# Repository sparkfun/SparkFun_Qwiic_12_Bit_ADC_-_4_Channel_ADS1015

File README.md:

SparkFun Qwiic ADC
========================================

[*SparkFun Qwiic 12 Bit ADC - 4 Channel ADS1015 (Sen-15334)*](https://www.sparkfun.com/products/15334)

Qwiic breakout board for the ADS1015 4-channel 12-bit ADC from TI.

A lot of the time you just need to add more analog inputs to solve a problem. It happens. The SparkFun Qwiic 12 Bit ADC can provide four channels of I2C controlled ADC input to your Qwiic enabled project. These channels can be used as single-ended inputs, or in pairs for differential inputs. What makes this even more powerful is that it has a programmable gain amplifier that lets you "zoom in" on a very small change in analog voltage (but will still effect your input range and resolution). Utilizing our handy Qwiic system, no soldering is required to connect it to the rest of your system. However, we still have broken out 0.1"-spaced pins in case you prefer to use a breadboard.

The ADS1015 uses its own internal voltage reference for measurements, but a ground and 3.3V reference are also available on the pin outs for users. This ADC board includes screw pin terminals on the four channels of input, allowing for solderless connection to voltage sources in your setup. It also has an address jumper that lets you choose one of four unique addresses (0x48, 0x49, 0x4A, 0x4B). With this, you can connect up to four of these on the same I2C bus and have sixteen channels of ADC. The maximum resolution of the converter is 12-bits in differential mode and 11-bits for single-ended inputs. Step sizes range from 125μV per count to 3mV per count depending on the full-scale range (FSR) setting.

We have included an onboard 10K trimpot connected to channel A3. This is handy for initial setup testing and can be used as a simple variable input to your project. But don't worry, we added an isolation jumper so you can use channel A3 however you'd like.

Repository Contents
-------------------

* **/Hardware** - Eagle design files (.brd, .sch)
* **/Production** - Production panel files (.brd)

Documentation
--------------
* **[Arduino Library for the ADS1015](https://github.com/sparkfun/SparkFun_ADS1015_Arduino_Library)** - Arduino library for the ADS1015.
* **[Hookup Guide](https://learn.sparkfun.com/tutorials/qwiic-12-bit-adc)** - Basic hookup guide for the SparkFun Qwiic 12 Bit ADC - 4 Channel ADS1015. Includes hardware overview, software installation instructions and overviews of each example in the arduino library.

License Information
-------------------

This product is _**open source**_! 

Please review the LICENSE.md file for license information. 

If you have any questions or concerns on licensing, please visit the [SparkFun Forum](https://forum.sparkfun.com/index.php) and post a topic. For more general questions related to our qwiic system, please visit this section of the forum: [SparkFun Forums: QWIIC SYSTEMS](https://forum.sparkfun.com/viewforum.php?f=105)

Distributed as-is; no warranty is given.

- Your friends at SparkFun.

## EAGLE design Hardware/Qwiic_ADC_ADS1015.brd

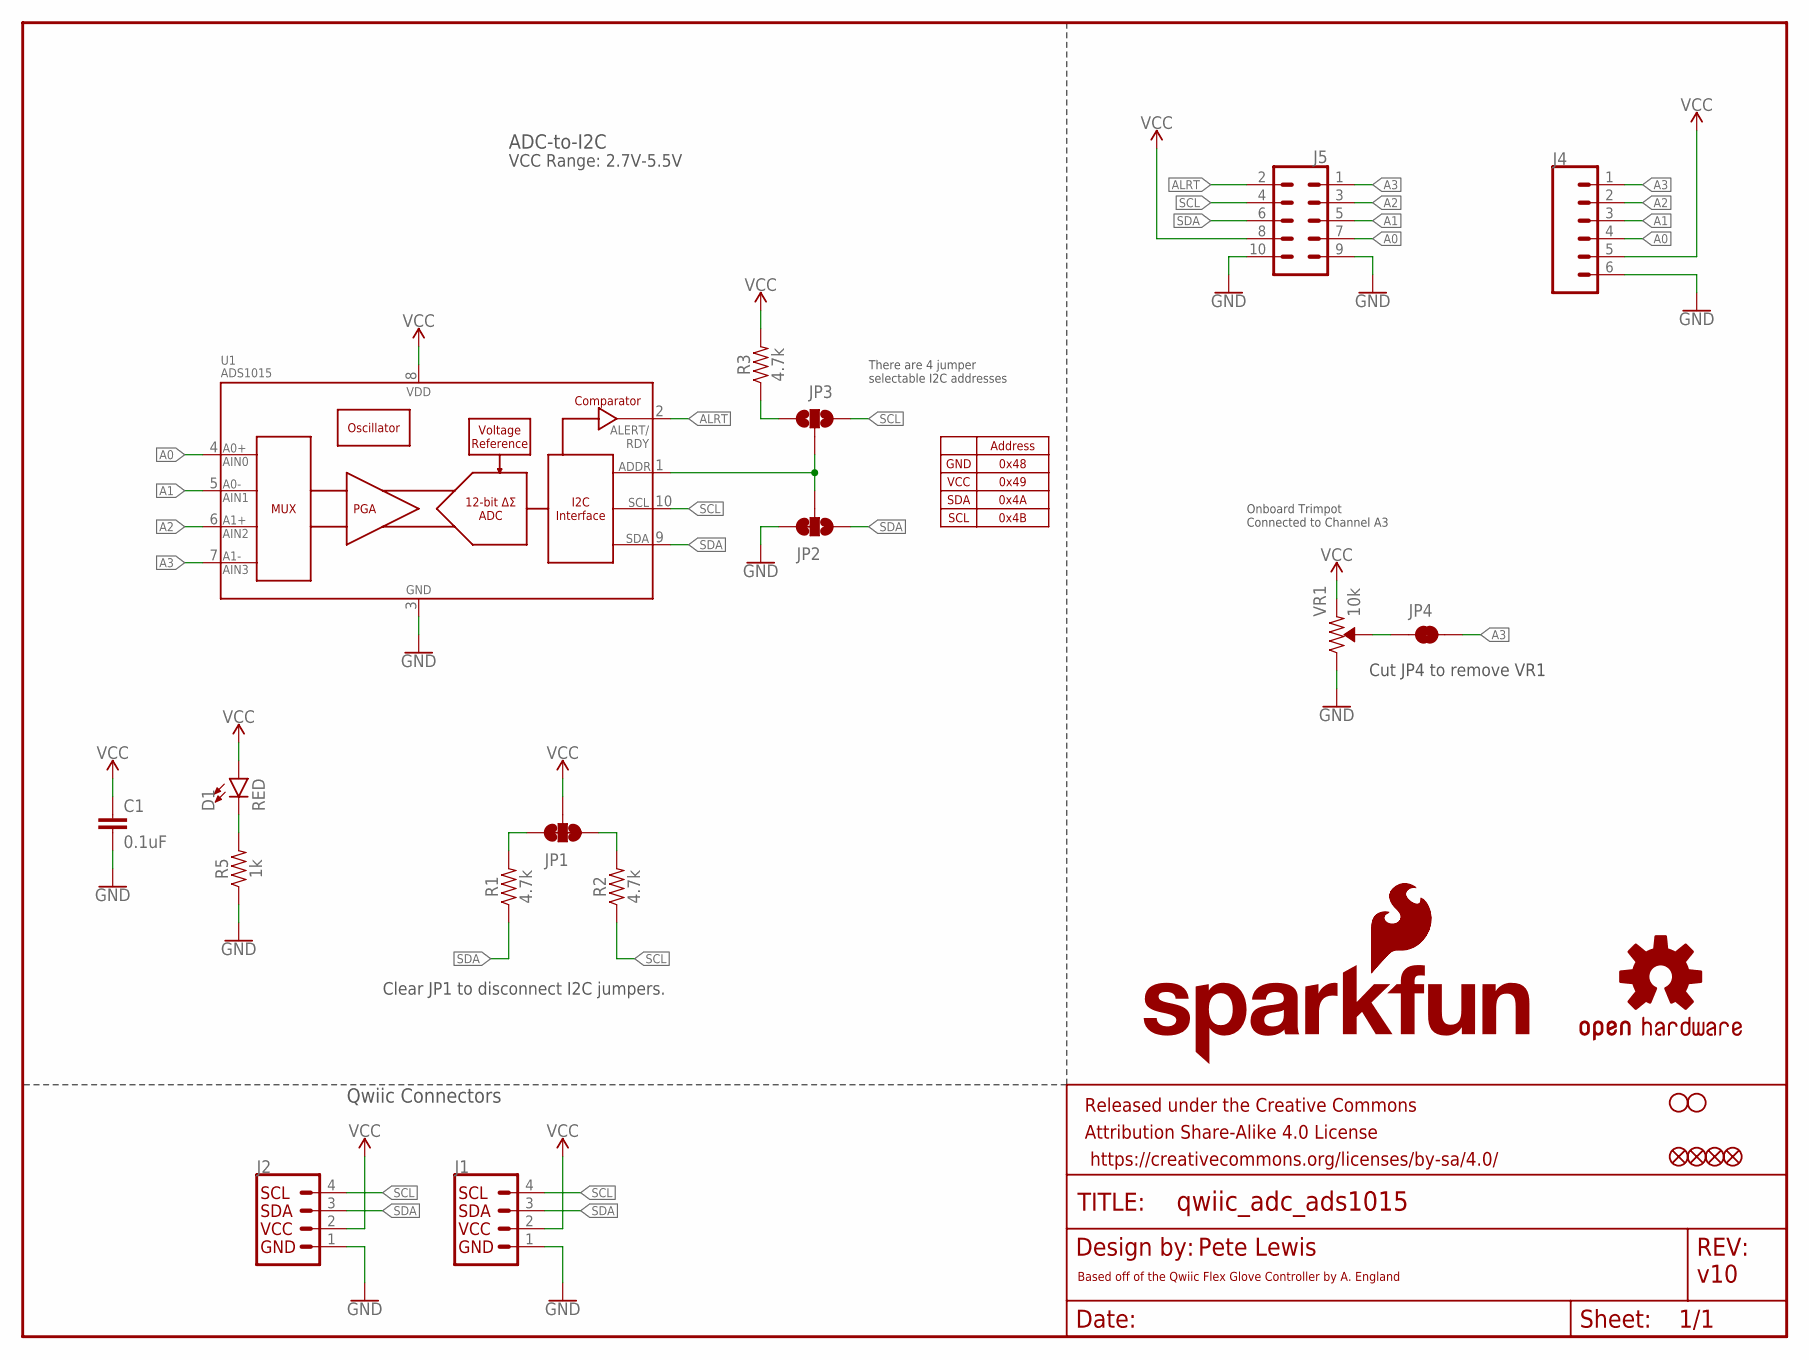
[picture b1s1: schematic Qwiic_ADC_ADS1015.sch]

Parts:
C1: 0.1uF; 0603
D1: RED; LED-0603
FD1, FD2, FD3, FD4: FIDUCIALUFIDUCIAL; FIDUCIAL-MICRO
FRAME1: FRAME-LETTER; CREATIVE_COMMONS
H1, H2: STAND-OFF
J1, J2: QWIIC_CONNECTORJS-1MM; JST04_1MM_RA
J4: Screw Pin Terminals; SCREWTERMINAL-3.5MM-6
J5: CONN_05X2NO_SILK; 2X5_NOSILK
JP1: JUMPER-SMT_3_2-NC_TRACE_NO-SILK; SMT-JUMPER_3_2-NC_TRACE_NO-SILK
JP2: JUMPER-SMT_3_1-NC_TRACE_NO-SILK; SMT-JUMPER_3_1-NC_TRACE_NO-SILK
JP3: JUMPER-SMT_3_NO_NO_SILK; SMT-JUMPER_3_0-NO_TRACE_NO-SILK
JP4: JUMPER-SMT_2_NC_TRACE_SILK; SMT-JUMPER_2_NC_TRACE_SILK
LOGO1: SFE_LOGO_NAME_FLAME.1_INCH; SFE_LOGO_NAME_FLAME_.1
LOGO2: OSHW-LOGOS; OSHW-LOGO-S
LOGO3: SFE_LOGO_FLAME.1_INCH; SFE_LOGO_FLAME_.1
R1, R2, R3: 4.7k; 0603
R5: 1k; 0603
U1: ADS1015; MSOP10
VR1: 10k; TRIMPOT-SMD-3MM-CLOSED

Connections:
A0: J4.4, J5.7, U1.4 (AIN0); also elsewhere on the board
A1: J4.3, J5.5, U1.5 (AIN1); also elsewhere on the board
A2: J4.2, J5.3, U1.6 (AIN2); also elsewhere on the board
A3: J4.1, J5.1, JP4.2, U1.7 (AIN3); also elsewhere on the board
ADDR: JP2.2, JP3.2, U1.1 (ADDR)
ALRT: J5.2, U1.2 (ALERT/RDY); also elsewhere on the board
GND: C1.2, J1.1, J2.1, J4.6, J5.9, J5.10, JP2.3, R5.1, U1.3 (VSS), VR1.3 (CW); also elsewhere on the board
unnamed: JP4.1, VR1.2 (WIPER)
unnamed 8: D1.C, R5.2; also elsewhere on the board
unnamed: JP3.1, R3.1
unnamed: JP1.1, R2.2
unnamed: JP1.3, R1.2
SCL: J1.4, J2.4, J5.4, JP3.3, R2.1, U1.10 (SCL); also elsewhere on the board
SDA: J1.3, J2.3, J5.6, JP2.1, R1.1, U1.9 (SDA); also elsewhere on the board
VCC: C1.1, D1.A, J1.2, J2.2, J4.5, J5.8, JP1.2, R3.2, U1.8 (VDD), VR1.1 (CCW); also elsewhere on the board

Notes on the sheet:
v10
Qwiic Connectors
ADC-to-I2C
Pete Lewis
There are 4 jumper selectable I2C addresses
Address
0x48
0x49
0x4A
0x4B
GND
VCC
SDA
SCL
VCC Range: 2.7V-5.5V
Clear JP1 to disconnect I2C jumpers.
Based off of the Qwiic Flex Glove Controller by A. England
Onboard Trimpot Connected to Channel A3
Cut JP4 to remove VR1

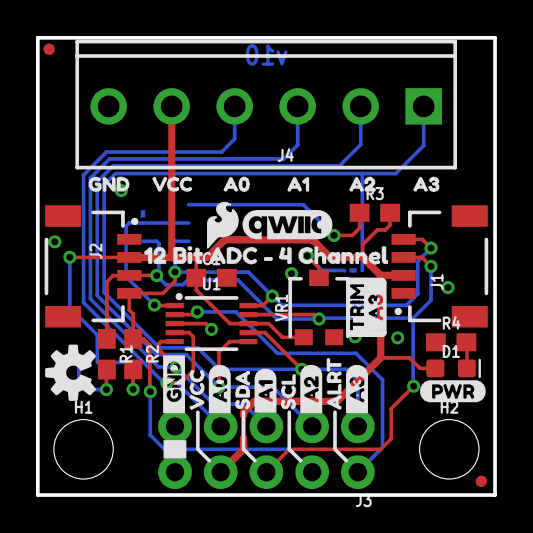
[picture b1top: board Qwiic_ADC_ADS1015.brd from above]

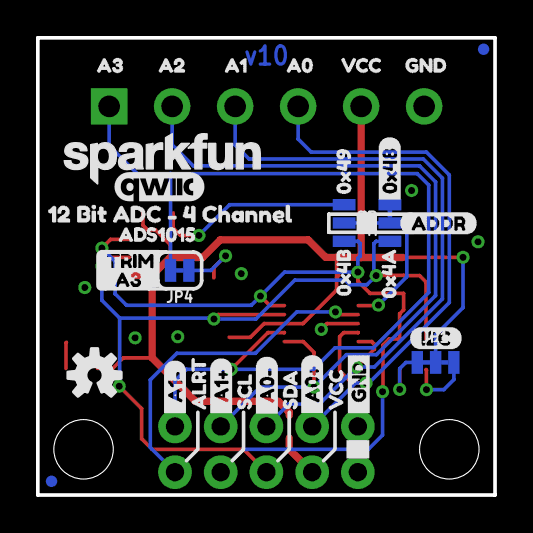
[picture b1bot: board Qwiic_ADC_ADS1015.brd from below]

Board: 2 copper layers, 25.4 x 25.4 mm, 73 parts (34 on the bottom side), 15 nets.

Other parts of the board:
J3: 2X5_NOSILK
R4: 1k; 0603
U$1, U$18, U$30, U$34: VCC1
U$2, U$35: GND0
U$3: 0X4A2
U$4: 0X491
U$5, U$36: A02
U$6, U$37: A13
U$7, U$38: A24
U$8, U$39: A35
U$9: _A0#3
U$10: _A0#4
U$11, U$19: TRIM7
U$12: 0X4B3
U$13: OSHW-LOGO-S
U$14: _A1#5
U$15: _A1#6
U$16, U$43: 12_BIT_ADC_#_4_CHANNEL1
U$17, U$22: _A3_0
U$20, U$29: _GND17
U$21, U$31: SDA6
U$23, U$32: SCL7
U$24, U$33: ALRT8
U$25: _A013
U$26: _A114
U$27: _A215
U$28: _A316
U$40: PWR0
U$41: I2C1
U$42: 0X480
U$44, U$47: QWIIC_5MM
U$45: ADDR0
U$46: ADS10150

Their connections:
A0: J3.7; also elsewhere on the board
A1: J3.5; also elsewhere on the board
A2: J3.3; also elsewhere on the board
A3: J3.1; also elsewhere on the board
ALRT: J3.2; also elsewhere on the board
GND: J3.9, J3.10, R4.1; also elsewhere on the board
unnamed 8: R4.2; also elsewhere on the board
SCL: J3.4; also elsewhere on the board
SDA: J3.6; also elsewhere on the board
VCC: J3.8; also elsewhere on the board

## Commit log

2019-04-15 Initial proto layout
2019-04-16 Hardware changes - pre-group review
    JP4 label changed to TRIM A0, also labeled trimpot on tops the same.
    Product name on bottom silk.
    Flipped pin order to have GND on left side of standard I2C pinout.
    Bottom labels now show differential inputs names (A0+, A0-, etc.)
    Added power LED, moved OSHW logo to bottom silk.
2019-04-16 updated product name silk
2019-04-16 ADDR label on jumper silk on bottom silk
2019-04-16 Group design review changes
    Moved Trimpot to A3 - so that initial use case can use A0 "as usual".
    Improved address jumper labeling
2019-04-17 Checklist changes pre double-check
    Cleaned up schematic.
    Added note for alert ready active high or low.
    Adjusted some small stuff for better ground pour flow.
    Added SS path on layer 47.
2019-04-18 updates post double-check - vias, measures, stubs
    1- nudged vias away from being under some silk
    2- added measures for distance between standoffs
    3- removed wire stubs.
    4-moved version in bottom copper to be clear of screw pin terminal bottom silk labels.
2019-05-22 renaming eagle files to match github repo and product name
2019-05-22 changed size of name text object to fit inside the schematic fram info box
2019-05-22 updated readme
    with live links, image, latest description and forum links
2019-05-24 Update Hookup Guide Link
    Added "hookup guide" to the name of the tutorial... changed the link address

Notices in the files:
parts and their libraries:
SparkFun-Aesthetics: Licensing: Creative Commons ShareAlike 4.0 International - https://creativecommons.org/licenses/by-sa/4.0
SparkFun-Aesthetics: Released under the Creative Commons Attribution Share-Alike 4.0 License
SparkFun-Aesthetics: https://creativecommons.org/licenses/by-sa/4.0
